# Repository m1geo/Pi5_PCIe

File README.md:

# Pi5 PCIe & M2 NVMe
A crude reverse engineering of the Raspberry Pi 5's FPC PCIe connector &amp; potential breakout board.

OFFICIAL RASPBERRY PI PCIE DOCOUMENTATION CAN BE FOUND HERE: https://datasheets.raspberrypi.com/pcie/pcie-connector-standard.pdf

In this bare-bones project I document a working PCIe pinout talk through my hardware tinkering to get the Raspberry Pi 5's PCIe connected to something. I had only seen Raspberry Pi's boards with their RP2040 and lots of parts on board. My professional experience with PCIe was that it either just goes or it really doesn't. I decided to try and make it do something for no reason other than the technical challenge.

To see what I did, check out my walkthrough of the process on YouTube: [Raspberry Pi 5 - Unofficial PCIe Success - Hacking the Pi5's PCIe into life](https://youtu.be/G5VOzO_ERTM).

**Note: This project is a reverse engineering - Please wait for/use the [official Raspberry Pi PCIe documentation](https://datasheets.raspberrypi.com/pcie/pcie-connector-standard.pdf) when using the PCIe FPC**

## Pi5 PCIe Breakout Board

The board is a quick test board. It could definitely be improved :)

## Pi5 M.2 NVMe Breakout Board

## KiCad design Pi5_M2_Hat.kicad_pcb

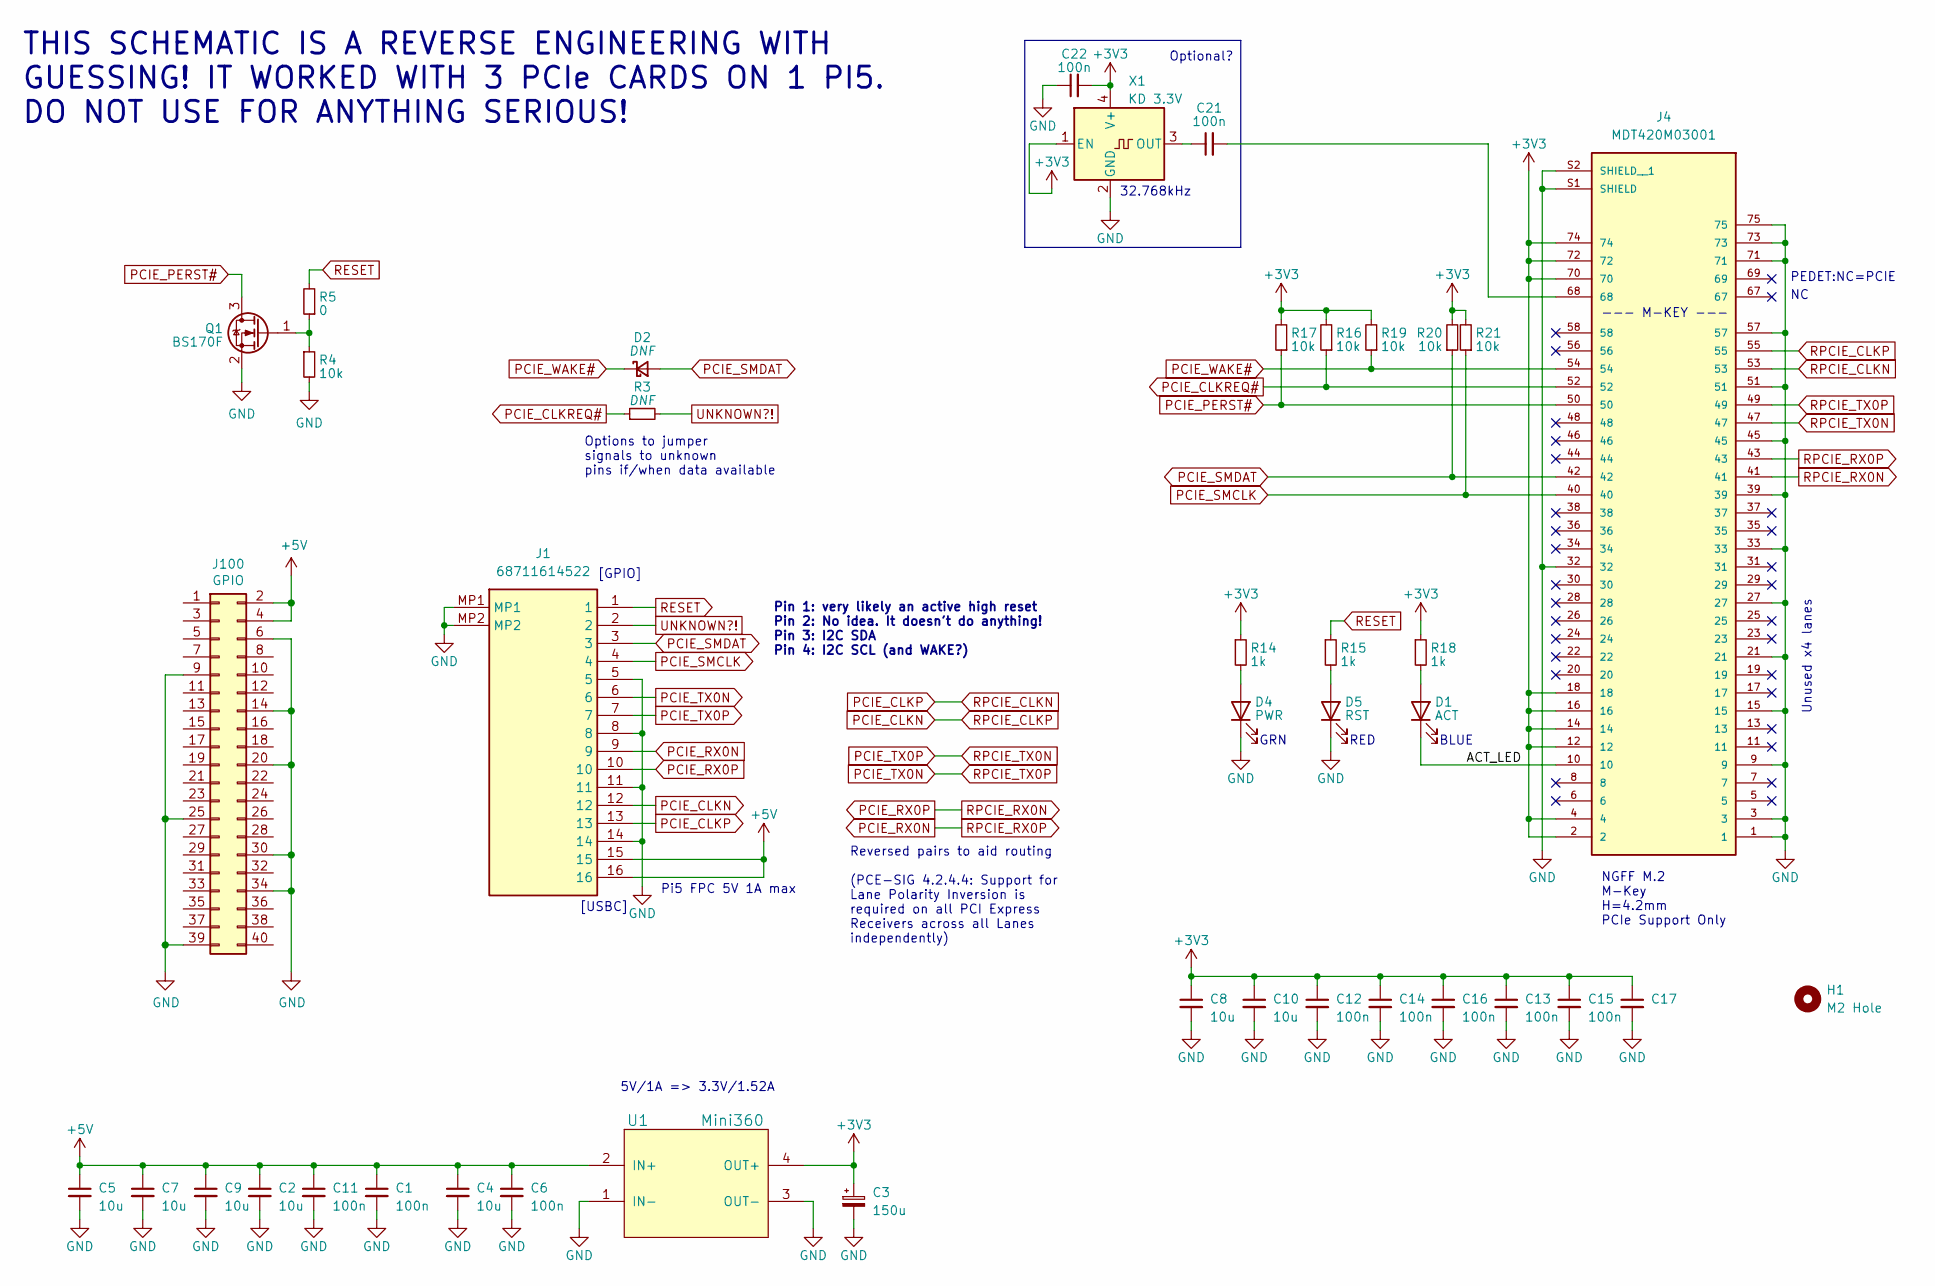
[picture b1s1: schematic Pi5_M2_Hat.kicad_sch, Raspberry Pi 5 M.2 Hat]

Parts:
C1, C6, C11, C12, C13, C14, C15, C16, C17, C21, C22: 100n; C_0805_2012Metric_Pad1.18x1.45mm_HandSolder
C2, C4, C5, C7, C8, C9, C10: 10u; C_0805_2012Metric_Pad1.18x1.45mm_HandSolder
C3: 150u; CP_Elec_6.3x7.7; LCSC C3032176
D1: ACT; LED_0805_2012Metric_Pad1.15x1.40mm_HandSolder
D2: DNF; D_0805_2012Metric_Pad1.15x1.40mm_HandSolder; LCSC C23848
D4: PWR; LED_0805_2012Metric_Pad1.15x1.40mm_HandSolder
D5: RST; LED_0805_2012Metric_Pad1.15x1.40mm_HandSolder
H1: M2 Hole; MountingHole_3.2mm_M3
J1: 68711614522; Manufacturer_Part_Number 68711614522; Mouser Part Number 710-68711614522
J4: MDT420M03001; AMPHENOL_MDT420M03001
J100: GPIO; PinSocket_2x20_P2.54mm_Vertical
Q1: BS170F; SOT-23
R3: DNF; R_0805_2012Metric_Pad1.20x1.40mm_HandSolder
R4, R16, R17, R19, R20, R21: 10k; R_0805_2012Metric_Pad1.20x1.40mm_HandSolder
R5: 0; R_0805_2012Metric_Pad1.20x1.40mm_HandSolder
R14, R15, R18: 1k; R_0805_2012Metric_Pad1.20x1.40mm_HandSolder
U1: Mini360; Mini360_step-down
X1: KD 3.3V; Oscillator_SMD_Fordahl_DFAS15-4Pin_5.0x3.2mm_HandSoldering

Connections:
+3V3: C3.1, C8.1, C10.1, C12.1, C13.1, C14.1, C15.1, C16.1, C17.1, C22.2, J4.2, J4.4, J4.12, J4.14, J4.16, J4.18, J4.70, J4.72, J4.74, R14.1, R16.2, R17.2, R18.1, R19.2, R20.2, R21.2, U1.4 (OUT+), X1.1 (EN), X1.4 (V+)
+5V: C1.1, C2.1, C4.1, C5.1, C6.1, C7.1, C9.1, C11.1, J1.15, J1.16, J100.2, J100.4, U1.2 (IN+)
/ACT_LED: D1.1 (K), J4.10
GND: C1.2, C2.2, C3.2, C4.2, C5.2, C6.2, C7.2, C8.2, C9.2, C10.2, C11.2, C12.2, C13.2, C14.2, C15.2, C16.2, C17.2, C22.1, D4.1 (K), D5.1 (K), J1.5, J1.8, J1.11, J1.14, J1.MP1, J1.MP2, J4.1, J4.3, J4.9, J4.15, J4.21, J4.27, J4.32, J4.33, J4.39, J4.45, J4.51, J4.57, J4.71, J4.73, J4.75, J4.S1 (SHIELD), J4.S2 (SHIELD__1), J100.6, J100.9, J100.14, J100.20, J100.25, J100.30, J100.34, J100.39, Q1.2 (S), R4.2, U1.1 (IN-), U1.3 (OUT-), X1.2 (GND)
unnamed: C21.2, J4.68
unnamed: D1.2 (A), R18.2
unnamed: D4.2 (A), R14.2
unnamed: D5.2 (A), R15.2
unnamed: Q1.1 (G), R4.1, R5.1
unnamed: C21.1, X1.3 (OUT)
PCIE_CLKN: J1.12, J4.55
PCIE_CLKP: J1.13, J4.53
PCIE_CLKREQ#: J4.52, R3.1, R16.1
PCIE_PERST#: J4.50, Q1.3 (D), R17.1
PCIE_RX0N: J1.9, J4.43
PCIE_RX0P: J1.10, J4.41
PCIE_SMCLK: J1.4, J4.40, R21.1
PCIE_SMDAT: D2.2 (A), J1.3, J4.42, R20.1
PCIE_TX0N: J1.6, J4.49
PCIE_TX0P: J1.7, J4.47
PCIE_WAKE#: D2.1 (K), J4.54, R19.1
RESET: J1.1, R5.2, R15.1
UNKNOWN?!: J1.2, R3.2

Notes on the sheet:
PEDET:NC=PCIE
BLUE
RED
THIS SCHEMATIC IS A REVERSE ENGINEERING WITH GUESSING! IT WORKED WITH 3 PCIe CARDS ON 1 PI5. DO NOT USE FOR ANYTHING SERIOUS!
[USBC]
--- M-KEY ---
Pin 1: very likely an active high reset Pin 2: No idea. It doesn't do anything! Pin 3: I2C SDA Pin 4: I2C SCL (and WAKE?)
32.768kHz
Options to jumper signals to unknown pins if/when data available
Optional?
Unused x4 lanes
Pi5 FPC 5V 1A max
Reversed pairs to aid routing (PCE-SIG 4.2.4.4: Support for Lane Polarity Inversion is required on all PCI Express Receivers across all Lanes independently)
NGFF M.2 M-Key H=4.2mm PCIe Support Only
[GPIO]
GRN
5V/1A => 3.3V/1.52A

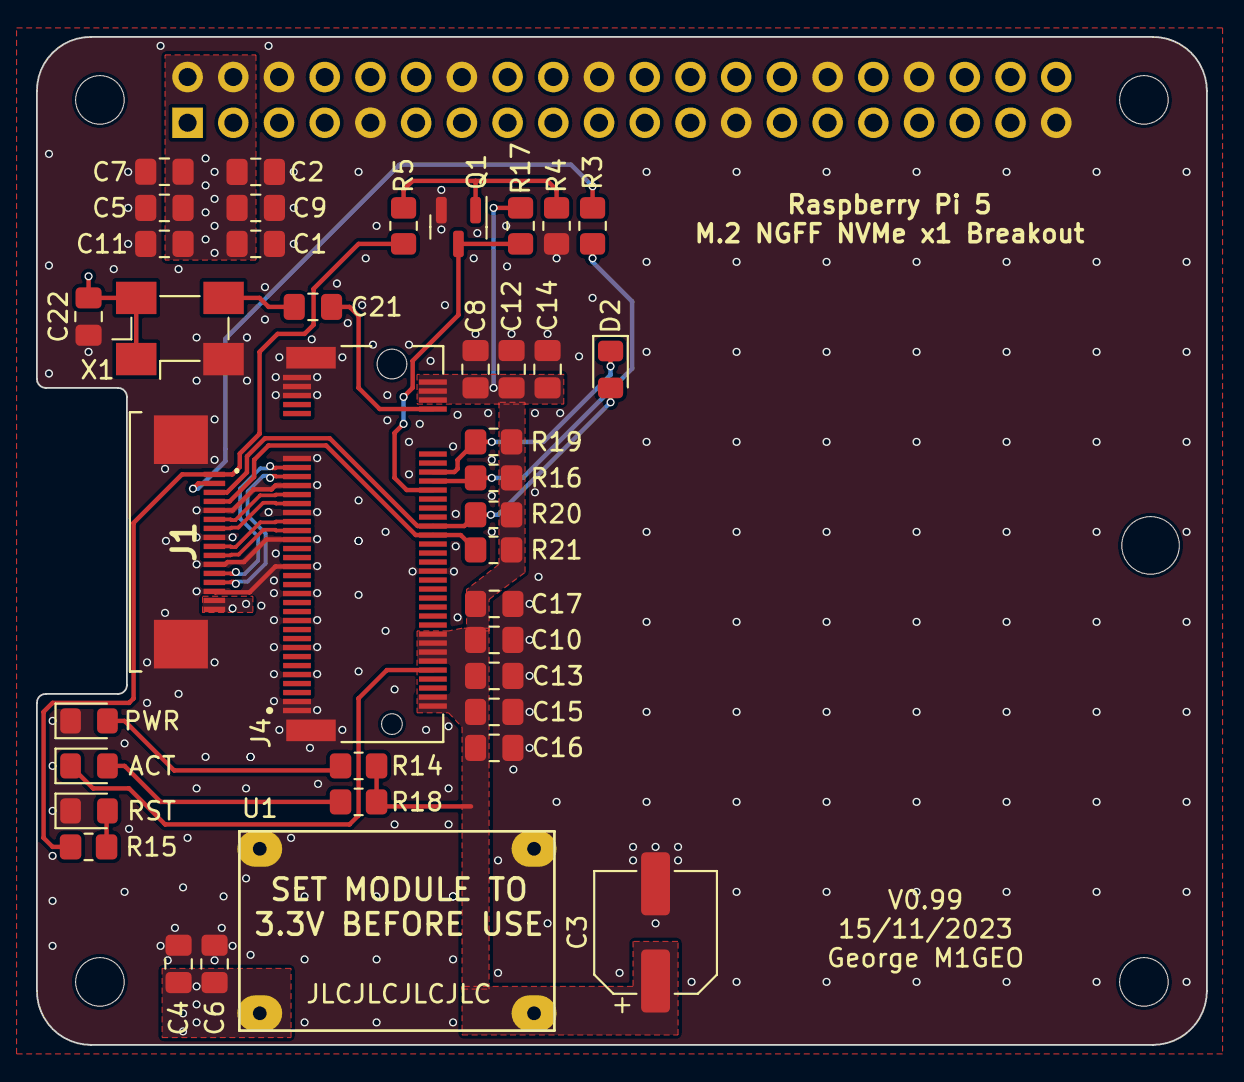
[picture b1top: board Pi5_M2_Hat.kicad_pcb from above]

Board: 4 copper layers, 65.0 x 56.0 mm, 45 parts (1 on the bottom side), 23 nets.

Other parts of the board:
MH1, MH2, MH3, MH4: MountingHole_2.7mm_M2.5

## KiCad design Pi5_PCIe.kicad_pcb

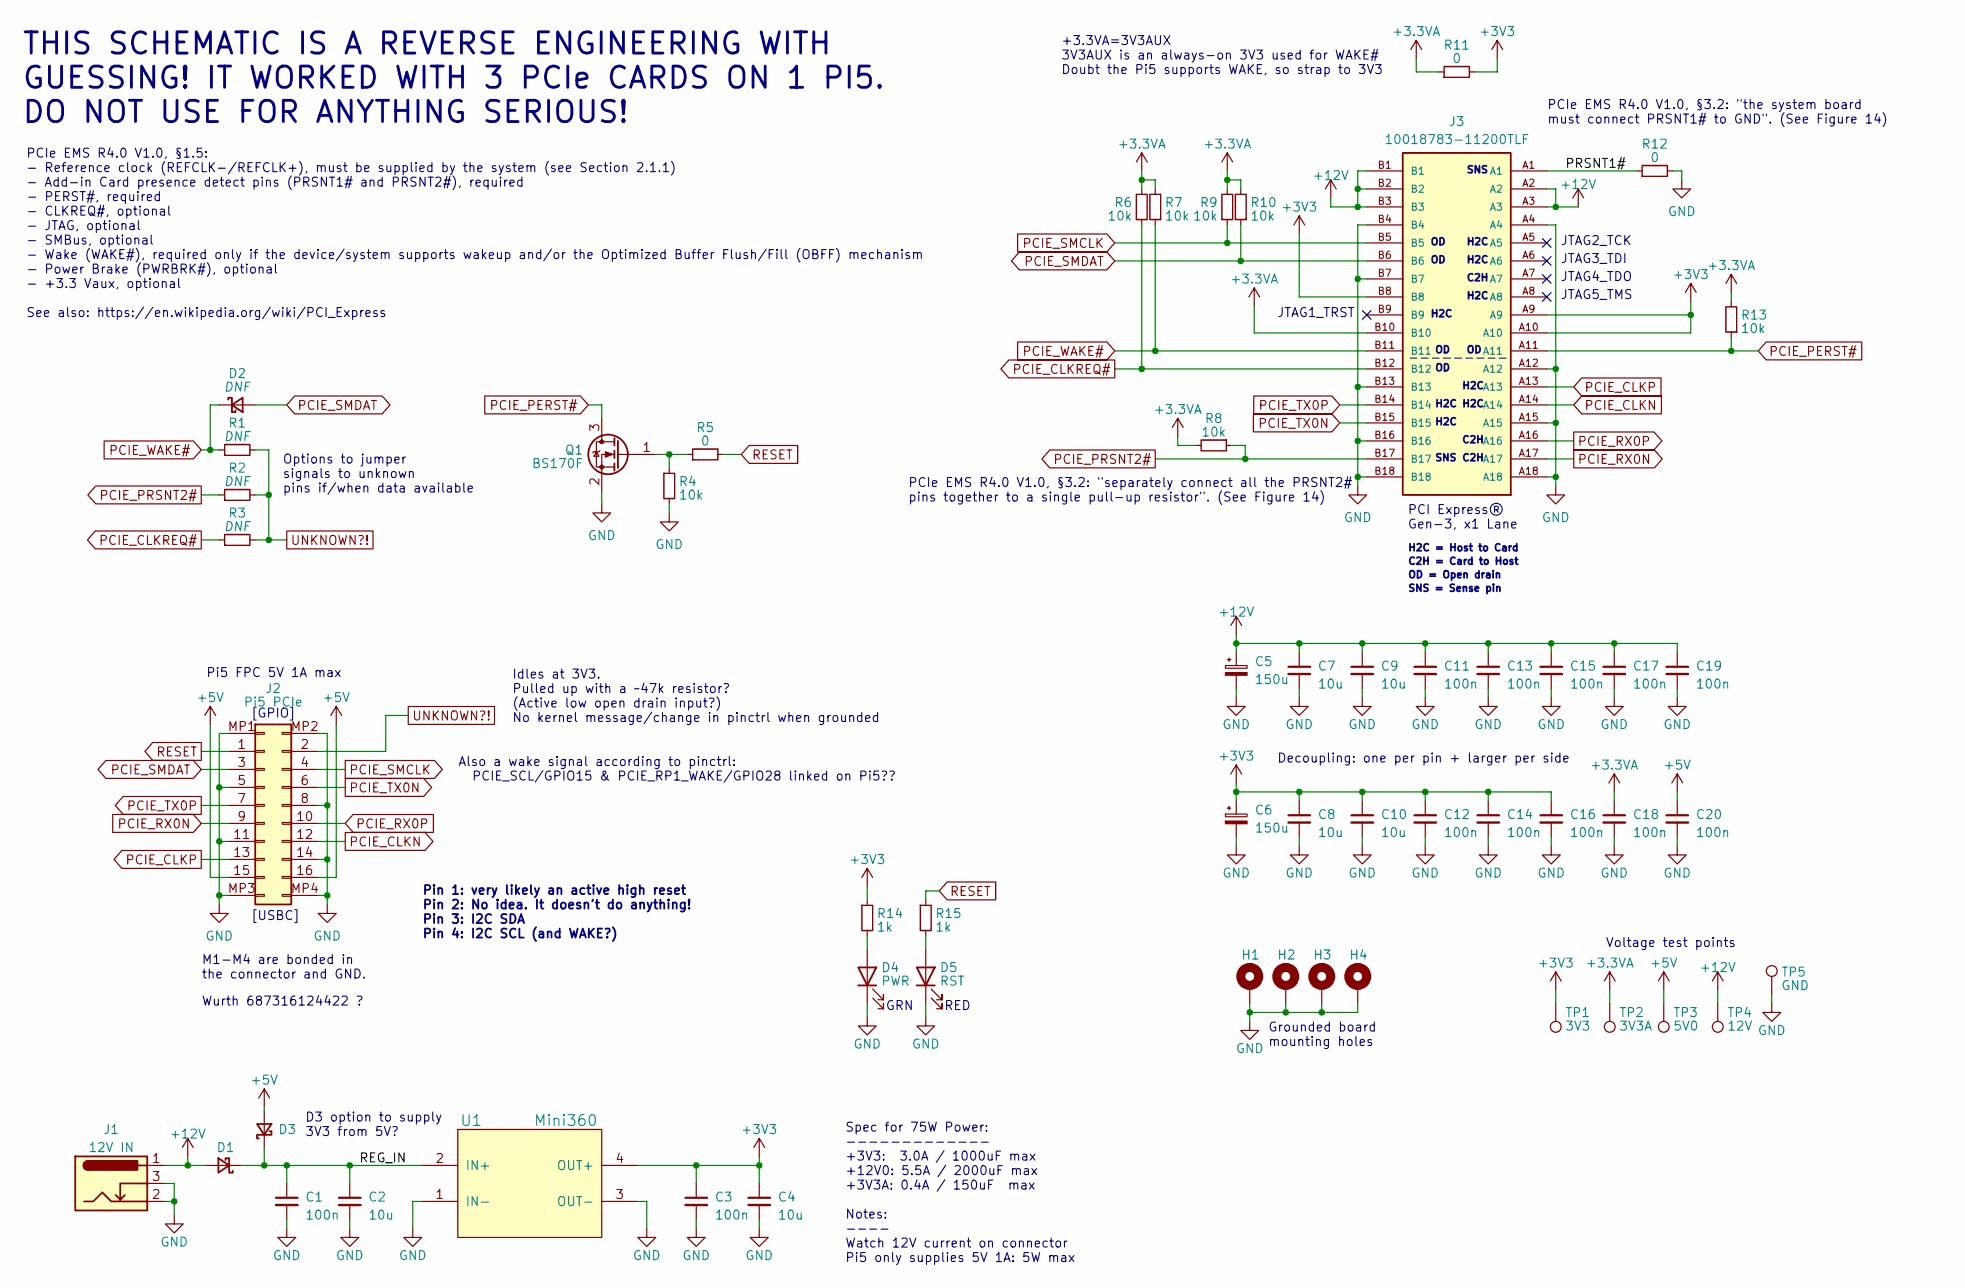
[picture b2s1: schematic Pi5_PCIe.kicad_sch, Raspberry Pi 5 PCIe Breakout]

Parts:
C1, C3, C11, C12, C13, C14, C15, C16, C17, C18, C19, C20: 100n; C_0805_2012Metric_Pad1.18x1.45mm_HandSolder
C2, C4, C7, C8, C9, C10: 10u; C_0805_2012Metric_Pad1.18x1.45mm_HandSolder
C5, C6: 150u; CP_Elec_6.3x7.7; LCSC C3032176
D1: (12V); D_SOD-123F; LCSC C23848
D2: DNF; D_0805_2012Metric_Pad1.15x1.40mm_HandSolder; LCSC C23848
D3: (5V); D_SOD-123F; LCSC C23848
D4: PWR; LED_0805_2012Metric_Pad1.15x1.40mm_HandSolder
D5: RST; LED_0805_2012Metric_Pad1.15x1.40mm_HandSolder
H1, H2, H3, H4: MountingHole_Pad; MountingHole_3.2mm_M3_Pad_Via
J1: 12V IN; BarrelJack_Horizontal; LCSC C319099
J2: Pi5 PCIe; 687316124422; MPN Wurth 687316124422
J3: 10018783-11200TLF; AMPHENOL_10018783-11200TLF; PARTREV Z
Q1: BS170F; SOT-23
R1, R2, R3: DNF; R_0805_2012Metric_Pad1.20x1.40mm_HandSolder
R4, R6, R7, R8, R9, R10, R13: 10k; R_0805_2012Metric_Pad1.20x1.40mm_HandSolder
R5, R11, R12: 0; R_0805_2012Metric_Pad1.20x1.40mm_HandSolder
R14, R15: 1k; R_0805_2012Metric_Pad1.20x1.40mm_HandSolder
TP1: 3V3; TestPoint_Pad_D1.5mm
TP2: 3V3A; TestPoint_Pad_D1.5mm
TP3: 5V0; TestPoint_Pad_D1.5mm
TP4: 12V; TestPoint_Pad_D1.5mm
TP5: GND; TestPoint_Pad_D1.5mm
U1: Mini360; Mini360_step-down

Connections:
+3.3VA: C18.1, J3.B10, R6.2, R7.2, R8.2, R9.2, R10.2, R11.1, R13.2, TP2.1
+3V3: C3.1, C4.1, C6.1, C8.1, C10.1, C12.1, C14.1, C16.1, J3.A9, J3.A10, J3.B8, R11.2, R14.1, TP1.1, U1.4 (OUT+)
+5V: C20.1, D3.2 (A), J2.15 (Pin_17), J2.16 (Pin_18), TP3.1
+12V: C5.1, C7.1, C9.1, C11.1, C13.1, C15.1, C17.1, C19.1, D1.2 (A), J1.1, J3.A2, J3.A3, J3.B1, J3.B2, J3.B3, TP4.1
/PRSNT1#: J3.A1, R12.1
/REG_IN: C1.1, C2.1, D1.1 (K), D3.1 (K), U1.2 (IN+)
GND: C1.2, C2.2, C3.2, C4.2, C5.2, C6.2, C7.2, C8.2, C9.2, C10.2, C11.2, C12.2, C13.2, C14.2, C15.2, C16.2, C17.2, C18.2, C19.2, C20.2, D4.1 (K), D5.1 (K), H1.1, H2.1, H3.1, H4.1, J1.2, J1.3, J2.5 (Pin_7), J2.8 (Pin_10), J2.11 (Pin_13), J2.14 (Pin_16), J2.MP1, J2.MP2, J2.MP3, J2.MP4, J3.A4, J3.A12, J3.A15, J3.A18, J3.B4, J3.B7, J3.B13, J3.B16, J3.B18, Q1.2 (S), R4.2, R12.2, TP5.1, U1.1 (IN-), U1.3 (OUT-)
unnamed: D4.2 (A), R14.2
unnamed: D5.2 (A), R15.2
unnamed: Q1.1 (G), R4.1, R5.1
PCIE_CLKN: J2.12 (Pin_14), J3.A14
PCIE_CLKP: J2.13 (Pin_15), J3.A13
PCIE_CLKREQ#: J3.B12, R3.1, R6.1
PCIE_PERST#: J3.A11, Q1.3 (D), R13.1
PCIE_PRSNT2#: J3.B17, R2.1, R8.1
PCIE_RX0N: J2.9 (Pin_11), J3.A17
PCIE_RX0P: J2.10 (Pin_12), J3.A16
PCIE_SMCLK: J2.4 (Pin_6), J3.B5, R9.1
PCIE_SMDAT: D2.2 (A), J2.3 (Pin_5), J3.B6, R10.1
PCIE_TX0N: J2.6 (Pin_8), J3.B15
PCIE_TX0P: J2.7 (Pin_9), J3.B14
PCIE_WAKE#: D2.1 (K), J3.B11, R1.1, R7.1
RESET: J2.1 (Pin_3), R5.2, R15.1
UNKNOWN?!: J2.2 (Pin_4), R1.2, R2.2, R3.2

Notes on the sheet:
JTAG3_TDI
C2H
RED
PCIe EMS R4.0 V1.0, §3.2: "the system board must connect PRSNT1# to GND". (See Figure 14)
H2C = Host to Card
C2H = Card to Host
Decoupling: one per pin + larger per side
JTAG4_TDO
---------
JTAG1_TRST
THIS SCHEMATIC IS A REVERSE ENGINEERING WITH GUESSING! IT WORKED WITH 3 PCIe CARDS ON 1 PI5. DO NOT USE FOR ANYTHING SERIOUS!
[USBC]
SNS = Sense pin
Pin 1: very likely an active high reset Pin 2: No idea. It doesn't do anything! Pin 3: I2C SDA Pin 4: I2C SCL (and WAKE?)
SNS
H2C
Voltage test points
+3.3VA=3V3AUX 3V3AUX is an always-on 3V3 used for WAKE# Doubt the Pi5 supports WAKE, so strap to 3V3
JTAG2_TCK
D3 option to supply 3V3 from 5V?
Wurth 687316124422 ?
Options to jumper signals to unknown pins if/when data available
PCIe EMS R4.0 V1.0, §1.5: - Reference clock (REFCLK-/REFCLK+), must be supplied by the system (see Section 2.1.1) - Add-in Card presence detect pins (PRSNT1# and PRSNT2#), required - PERST#, required - CLKREQ#, optional - JTAG, optional - SMBus, optional - Wake (WAKE#), required only if the device/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
PCI Express® Gen-3, x1 Lane
Spec for 75W Power: ------------- +3V3: 3.0A / 1000uF max +12V0: 5.5A / 2000uF max +3V3A: 0.4A / 150uF max Notes: ---- Watch 12V current on connector Pi5 only supplies 5V 1A: 5W max
Also a wake signal according to pinctrl: PCIE_SCL/GPIO15 & PCIE_RP1_WAKE/GPIO28 linked on Pi5??
Pi5 FPC 5V 1A max
Grounded board mounting holes
JTAG5_TMS
M1-M4 are bonded in the connector and GND.
Idles at 3V3. Pulled up with a ~47k resistor? (Active low open drain input?) No kernel message/change in pinctrl when grounded
PCIe EMS R4.0 V1.0, §3.2: "separately connect all the PRSNT2# pins together to a single pull-up resistor". (See Figure 14)
[GPIO]
OD = Open drain
GRN

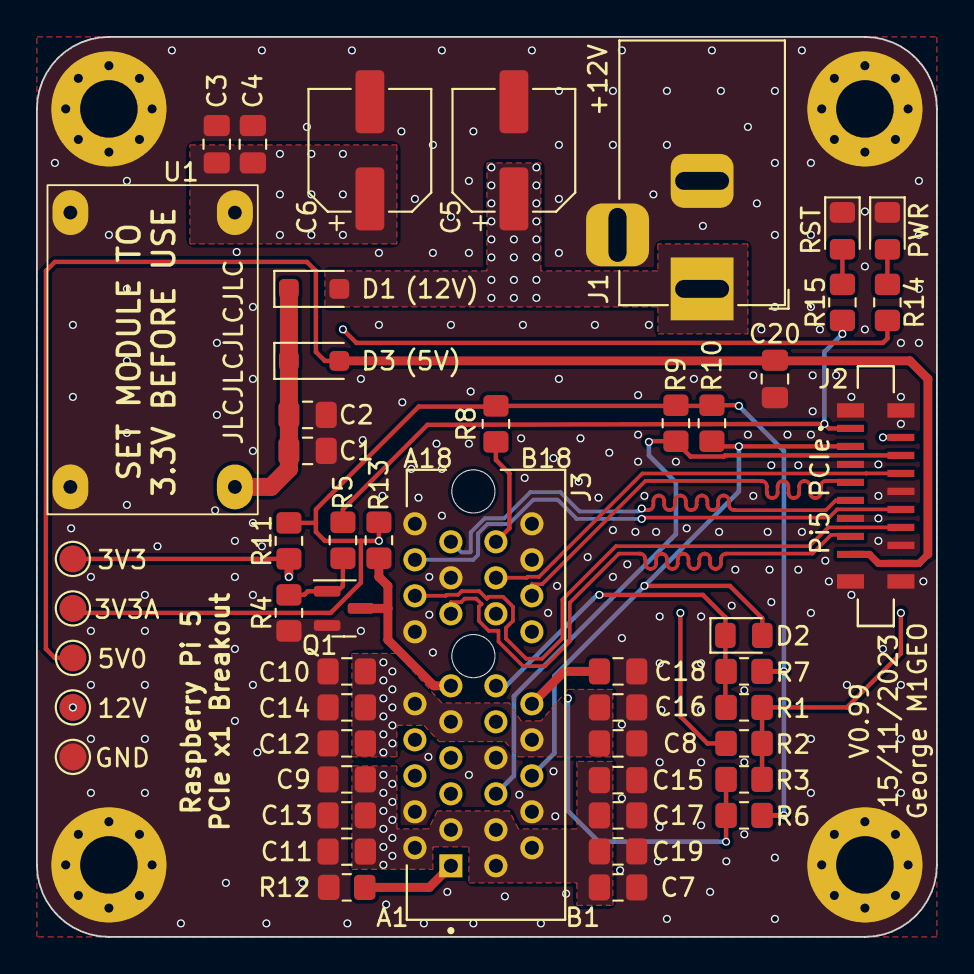
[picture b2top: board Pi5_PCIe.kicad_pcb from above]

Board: 4 copper layers, 50.0 x 50.0 mm, 54 parts (0 on the bottom side), 24 nets.

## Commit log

2023-11-06 Added PDF schematic for easier viewing
2023-11-07 Updated readme to clarify the documentation stance
2023-11-07 Schematic tweaks towards making a test PCB
2023-11-09 Added scope print of pin1 toggling high on startup
2023-11-09 Updated schematic based on testing & PCB layout * Used pinctrl to find out what P3 & P4 did, as suggested by @trejan * Reviewed Pi5 layout under connector to see that I had RX(P|N) swapped
2023-11-10 Library files tidyup
2023-11-11 Quick test PCIe breakout board
2023-11-15 Created Gerbers for board v0.99 & tagged
2023-12-08 Added official RasPi link
